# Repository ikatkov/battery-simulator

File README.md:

# Electronic battery simulator (also works as 35W electronic load)

## Description

Useful for testing battery chargers. 
Designed to use from single lithium batteries to 5S packs i.e. from 3.7V to 18V. Max charging current 2.3A 

Set the "battery" voltage with coarse/fine voltage pots, connect the charger and start the charging process. 
Adjust the "battery" voltage up/down to test how the charger responds. Set max allowed "charge" current with the current pot.

This device simulates battery discharging, current is limited by 200 Ohm resistors i.e. 60-120mA. When in "discharge" mode the
green LED is lit.
When the device simulates battery charging - the current is limited by both the internal charger circuitry and max allowed "charge" current. 
The absolute max is ~2.3A When in "charge" mode the red LED is lit.

A note on `*S` packs:
A typical pack charger senses the voltage across each battery in the pack. This is not implemented inside
but can be built as a pluggable add-on. One side plugs into the banana input of this electronic battery simulator, and the other side forms multiple voltage dividers, as many as the charger wants. Example

### Input voltage
Input voltage (VCC): 12-24V. The max "battery" voltage one can set is ~3V below this. 

* LM358 output swing from the top rail is 1.5V
* BJT voltage drop 0.7V
* Diode voltage drop 0.7V

Max voltage available to the cooling fan is ~2.75V below VCC. For the maximum cooling, VCC should be 14V+

* LM358 output swing from the top rail is 1.5V
* LM317 ADJ-to-out is 1.25V

### Charger voltage
Charger voltage 0-20V. This is limited by the MOSFET Vds

## Usage

Typical examples:

* manually increase the voltage to 4.2V and expect the lithium battery charger to stop
* manually limit/reduce the max allowed charging current, simulating increased battery resistance, and expect the charger to stop

Non-typical example:

* Set min "battery" voltage, apply external power, and use as a dummy load.

## Limits

Do not exceed 35W continuous heat dissipation. Pass BJT transistor will blow.

Do not exceed 20V charger voltage, switch MOSFET will blow.

Do not exceed 30V input voltage, opamps will blow.

## Fabrication

[LTSpice](ltspice)

[Schematic](schematic.pdf)

[Kicad](kicad)

[Enclosure, knobs](fusion360)

[Notes on fabricating metal enclosures](Metal%20enclosure%20project%20box.md)

Heatsink is not shown on the render below

## Notes

The main surprise is that this thing is as usable as a general-purpose dummy load as much as an electronic battery itself.

Do not make daughter boards that have buttons or pots. Mount them separately, and connect them with wires. It is wobbly, the daughter board needs to be secured to a vertical panel, while the vertical panel needs to be removable by design. Total PITA, don't do it again.

Despite PCB being sparsely populated, wires make the inside of the box very very crowded. Need to make the box deeper, +1-2-3 cm depth would not be noticeable but would make wire management easier.

Make the cooling fan blow air on the heat sink along the fins.

This can't be stressed enough - position all connectors, mounting holes and heatsink on the PCB before routing.

See [Notes on fabricating metal enclosures](Metal%20enclosure%20project%20box.md)

For a small enclosure like here, it takes longer to manufacture from metal than to 3D print.

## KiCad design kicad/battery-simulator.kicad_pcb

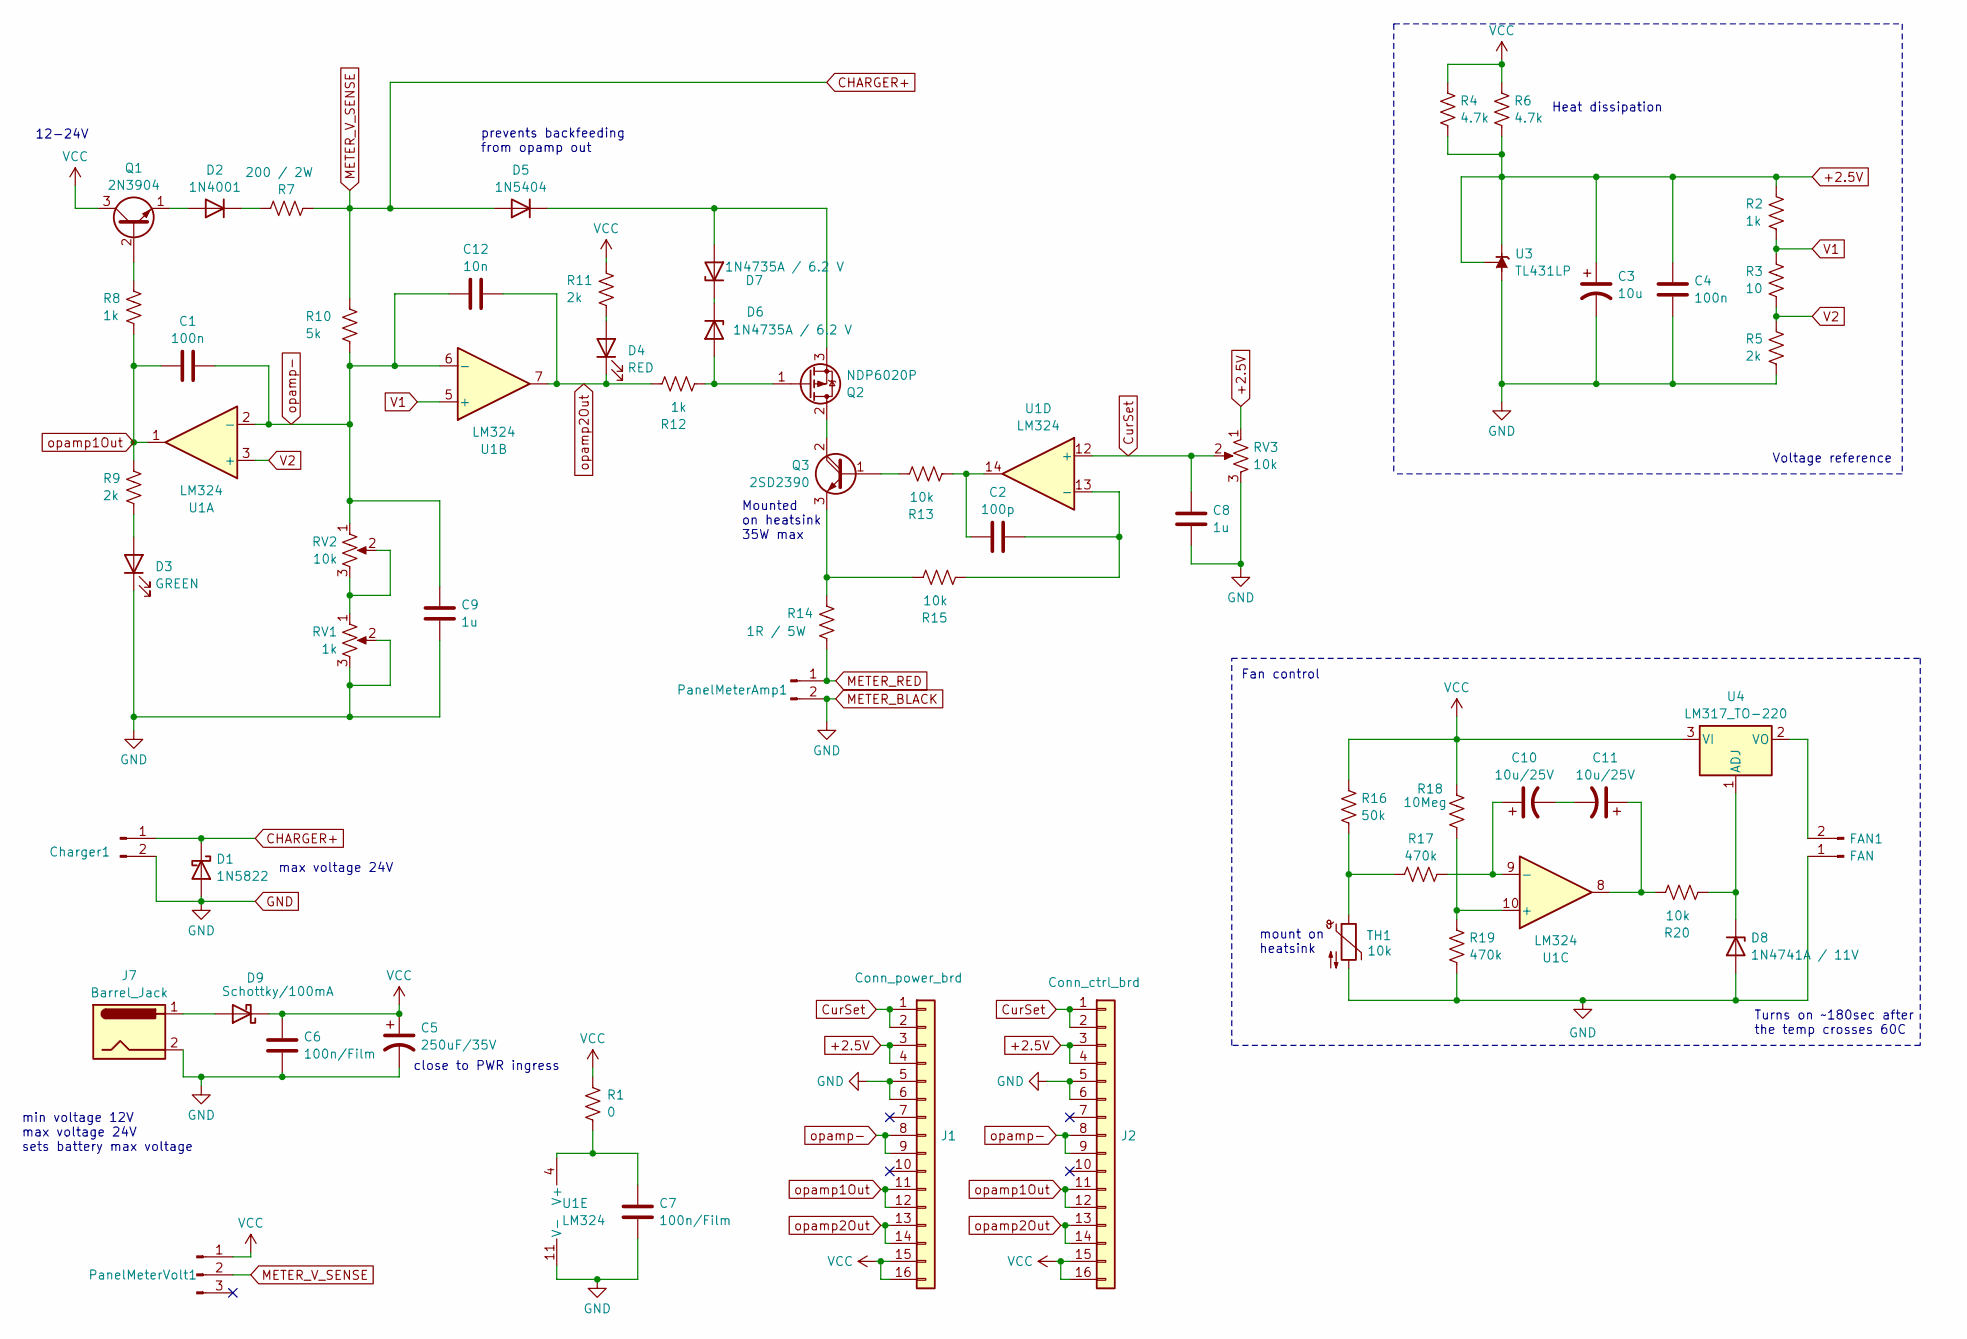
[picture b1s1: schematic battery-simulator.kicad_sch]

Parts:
C1, C4: 100n; C_1206_3216Metric
C2: 100p; C_1206_3216Metric
C3: 10u; CP_Radial_D5.0mm_P2.50mm
C5: 250uF/35V; CP_Radial_D14.0mm_P5.00mm
C6, C7: 100n/Film; C_1206_3216Metric
C8, C9: 1u; C_1206_3216Metric
C10, C11: 10u/25V; CP_Radial_D5.0mm_P2.50mm
C12: 10n; C_1206_3216Metric
Charger1: Charger; PhoenixContact_MCV_1,5_2-G-5.08_1x02_P5.08mm_Vertical
D1: 1N5822; D_DO-201AD_P5.08mm_Vertical_AnodeUp
D2: 1N4001; D_DO-41_SOD81_P10.16mm_Horizontal
D3: GREEN; LED_D5.0mm
D4: RED; LED_D5.0mm
D5: 1N5404; D_DO-201AD_P15.24mm_Horizontal
D6, D7: 1N4735A / 6.2 V; D_DO-35_SOD27_P5.08mm_Vertical_KathodeUp
D8: 1N4741A / 11V; D_DO-35_SOD27_P5.08mm_Vertical_KathodeUp
D9: Schottky/100mA; D_SMA
FAN1: FAN; PinHeader_1x03_P2.54mm_Vertical
J1: Conn_power_brd; PinSocket_1x16_P2.54mm_Vertical
J2: Conn_ctrl_brd; PinHeader_1x16_P2.54mm_Horizontal
J7: Barrel_Jack; BarrelJack_Horizontal
PanelMeterAmp1: Panel Meter Amp; PhoenixContact_MCV_1,5_2-G-5.08_1x02_P5.08mm_Vertical
PanelMeterVolt1: Panel Meter Volt; JST_XH_B3B-XH-A_1x03_P2.50mm_Vertical
Q1: 2N3904; TO-92L_Wide
Q2: NDP6020P; TO-220-3_Vertical
Q3: 2SD2390; TO-3P-3_Vertical
R1: 0; R_1206_3216Metric
R2, R8, R12: 1k; R_0805_2012Metric
R3: 10; R_0805_2012Metric
R4, R6: 4.7k; R_Axial_DIN0207_L6.3mm_D2.5mm_P7.62mm_Horizontal
R5, R9, R11: 2k; R_0805_2012Metric
R7: 200 / 2W; R_Axial_Power_L20.0mm_W6.4mm_P22.40mm
R10: 5k; R_Axial_DIN0207_L6.3mm_D2.5mm_P7.62mm_Horizontal
R13, R15, R20: 10k; R_0805_2012Metric
R14: 1R / 5W; R_Axial_Power_L25.0mm_W9.0mm_P27.94mm
R16: 50k; R_0805_2012Metric
R17: 470k; R_1206_3216Metric
R18: 10Meg; R_0805_2012Metric
R19: 470k; R_0805_2012Metric
RV1: 1k; Potentiometer_Bourns_PTV09A-1_Single_Vertical
RV2, RV3: 10k; Potentiometer_Bourns_PTV09A-1_Single_Vertical
TH1: 10k; JST_XH_B2B-XH-A_1x02_P2.50mm_Vertical
U1: LM324; DIP-14_W7.62mm_Socket
U3: TL431LP; TO-92L_Wide
U4: LM317_TO-220; TO-220-3_Vertical

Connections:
+2.5V: C3.1, C4.2, J1.3, J1.4, J2.3, J2.4, R2.1, R4.2, R6.2, RV3.1, U3.1 (REF), U3.3 (K)
CHARGER+: Charger1.1, D1.1 (K), D5.2 (A), PanelMeterVolt1.2, R7.2, R10.1
CurSet: C8.2, J1.1, J1.2, J2.1, J2.2, RV3.2, U1.12 (+)
GND: C3.2, C4.1, C5.2, C6.1, C7.1, C8.1, C9.1, Charger1.2, D1.2 (A), D3.1 (K), D8.2 (A), FAN1.1, J1.5, J1.6, J2.5, J2.6, J7.2, PanelMeterAmp1.2, R5.2, R19.2, RV1.2, RV1.3, RV3.3, TH1.2, U1.11 (V-), U3.2 (A)
METER_RED: PanelMeterAmp1.1, R14.2
unnamed: C2.2, R13.2, U1.14
unnamed: C10.2, C11.2
unnamed: C11.1, R20.1, U1.8
unnamed: D2.2 (A), Q1.1 (E)
unnamed: D2.1 (K), R7.1
unnamed: D3.2 (A), R9.2
unnamed: D4.2 (A), R11.2
unnamed: D5.1 (K), D7.2 (A), Q2.3 (S)
unnamed: D6.2 (A), Q2.1 (G), R12.2
unnamed: D6.1 (K), D7.1 (K)
unnamed: D8.1 (K), R20.2, U4.1 (ADJ)
unnamed: D9.2 (A), J7.1
unnamed: FAN1.2, U4.2 (VO)
unnamed: Q1.2 (B), R8.1
unnamed: Q2.2 (D), Q3.2 (C)
unnamed: Q3.1 (B), R13.1
unnamed: Q3.3 (E), R14.1, R15.1
unnamed: R16.2, R17.1, TH1.1
unnamed: RV1.1, RV2.2, RV2.3
unnamed: R18.2, R19.1, U1.10 (+)
unnamed: C10.1, R17.2, U1.9 (-)
unnamed: C2.1, R15.2, U1.13 (-)
unnamed: C7.2, R1.2, U1.4 (V+)
V1: R2.2, R3.1, U1.5 (+)
V2: R3.2, R5.1, U1.3 (+)
VCC: C5.1, C6.2, D9.1 (K), J1.15, J1.16, J2.15, J2.16, PanelMeterVolt1.1, Q1.3 (C), R1.1, R4.1, R6.1, R11.1, R16.1, R18.1, U4.3 (VI)
opamp1Out: C1.2, J1.11, J1.12, J2.11, J2.12, R8.2, R9.1, U1.1
opamp2Out: C12.1, D4.1 (K), J1.13, J1.14, J2.13, J2.14, R12.1, U1.7
opamp-: C1.1, C9.2, C12.2, J1.8, J1.9, J2.8, J2.9, R10.2, RV2.1, U1.2 (-), U1.6 (-)

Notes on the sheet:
min voltage 12V max voltage 24V sets battery max voltage
close to PWR ingress
mount on heatsink
Voltage reference
max voltage 24V
Mounted on heatsink 35W max
Turns on ~180sec after the temp crosses 60C
prevents backfeeding from opamp out
12-24V
Fan control
Heat dissipation

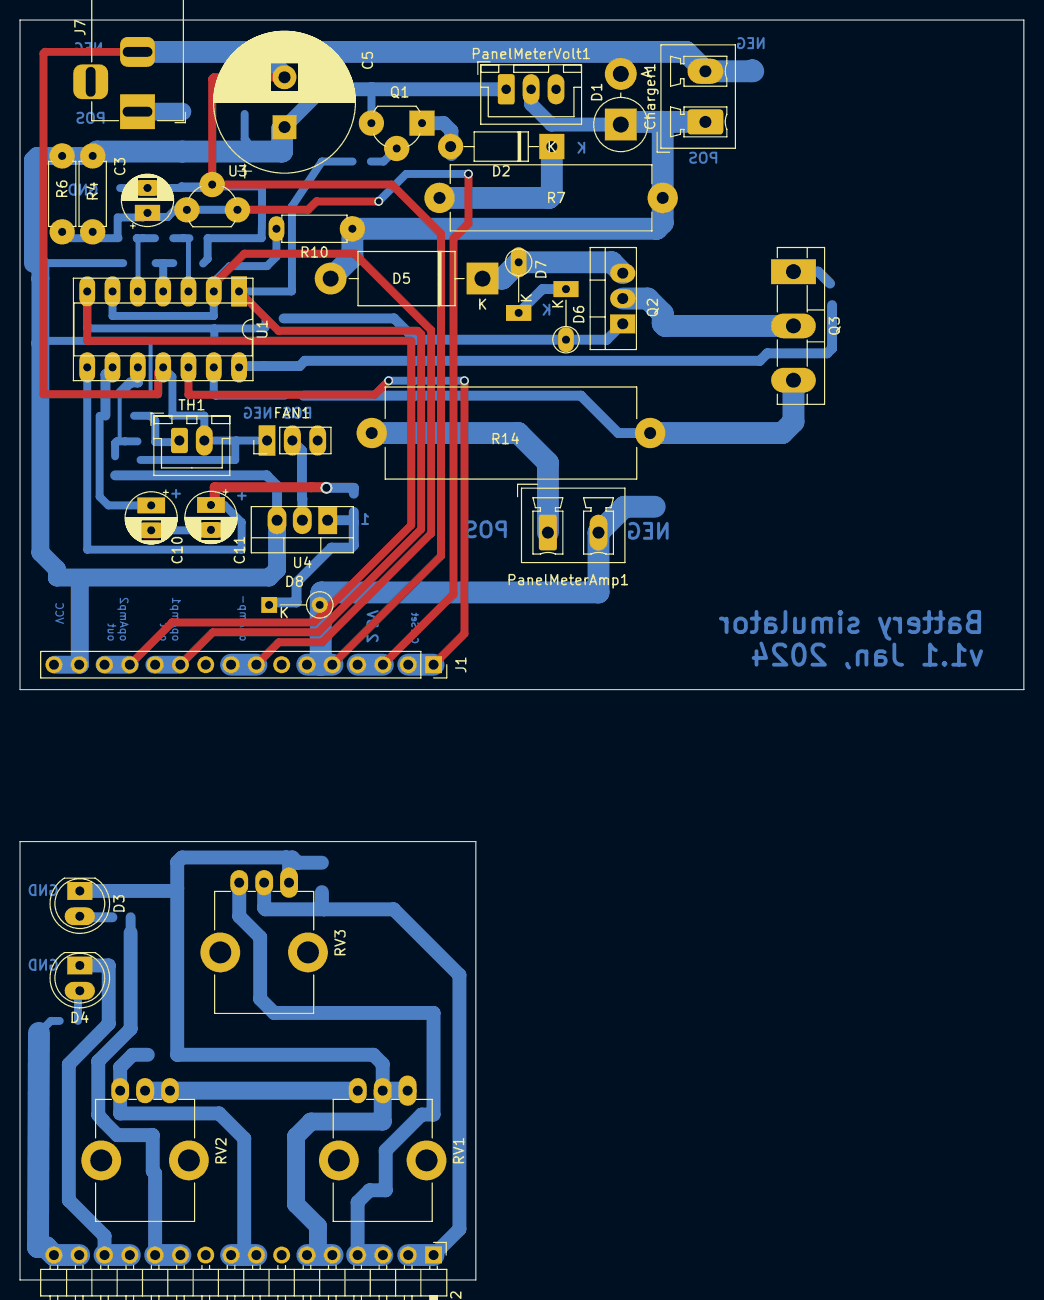
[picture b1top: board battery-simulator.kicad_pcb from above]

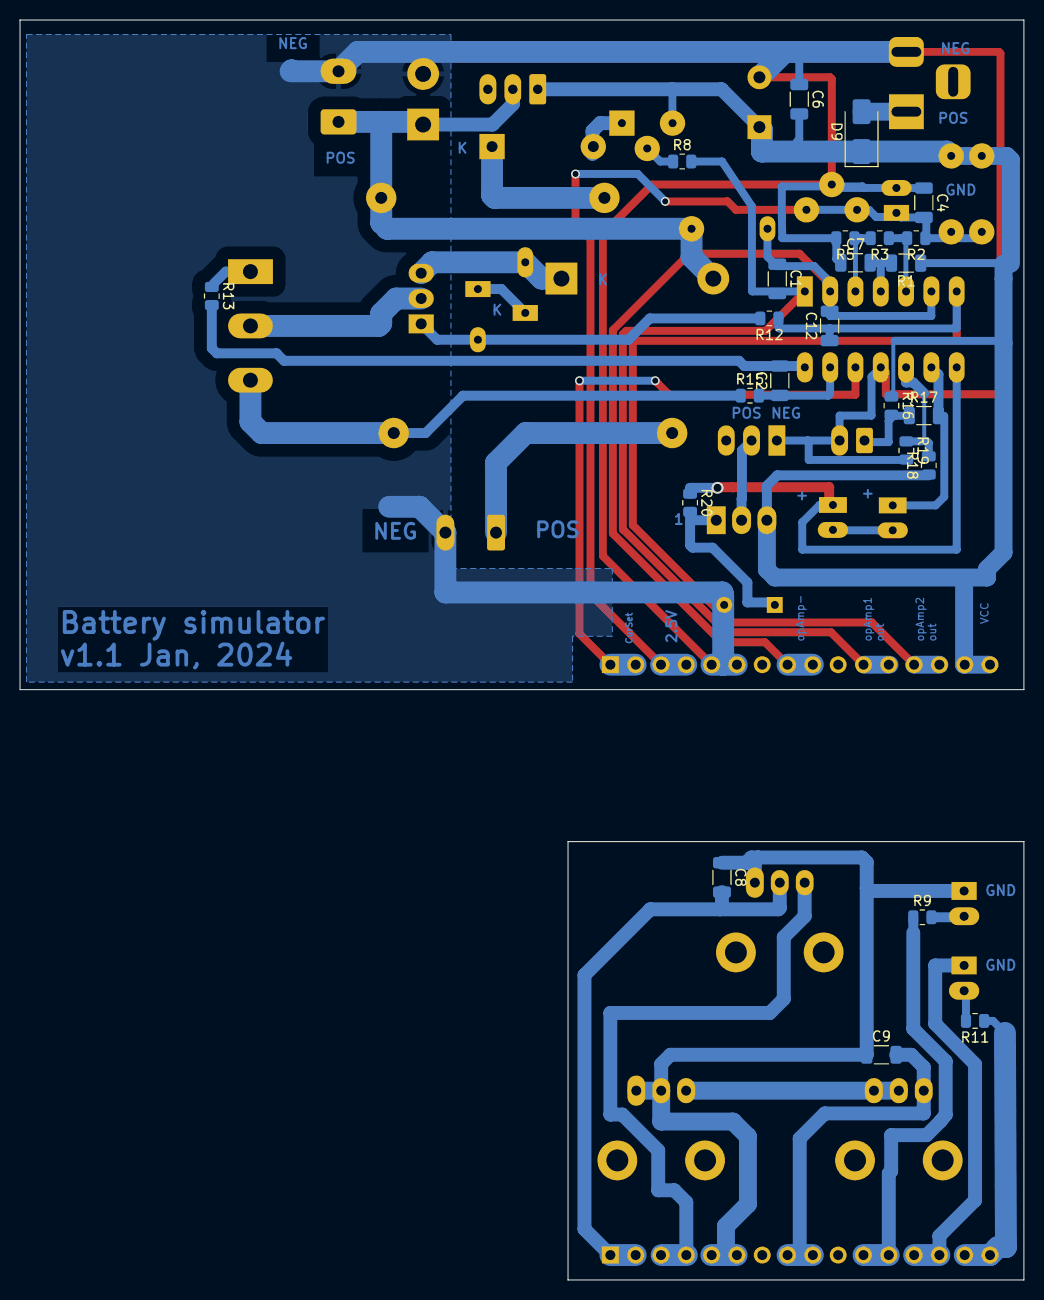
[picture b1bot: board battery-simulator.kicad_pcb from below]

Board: 4 copper layers, 100.8 x 126.5 mm, 58 parts (24 on the bottom side), 34 nets.

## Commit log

2024-01-17 More ideas
2024-01-18 minor edits
2024-01-18 add knobs models
2024-01-18 minor ltspice fix
